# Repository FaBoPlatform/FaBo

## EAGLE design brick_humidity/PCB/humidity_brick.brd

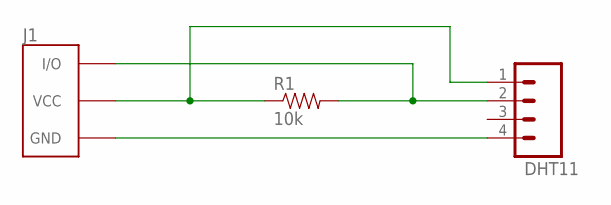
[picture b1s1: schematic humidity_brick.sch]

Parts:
J1: BRICK_3PIN
JP1: DHT11; 1X04_LONGPADS
R1: 10k; AXIAL-0.4

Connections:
GND: J1.GND, JP1.4
unnamed: J1.IN/OUT (I/O), JP1.2, R1.P$2 (2)
unnamed: J1.VCC, JP1.1, R1.P$1 (1)

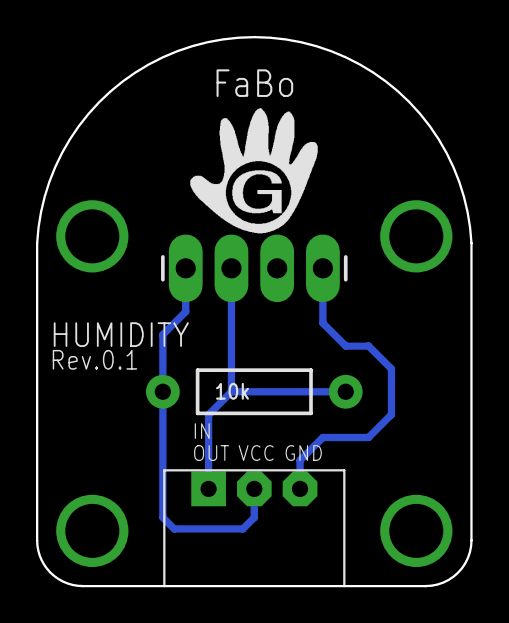
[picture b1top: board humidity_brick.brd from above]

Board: 2 copper layers, 24.1 x 30.5 mm, 3 parts (0 on the bottom side), 3 nets.

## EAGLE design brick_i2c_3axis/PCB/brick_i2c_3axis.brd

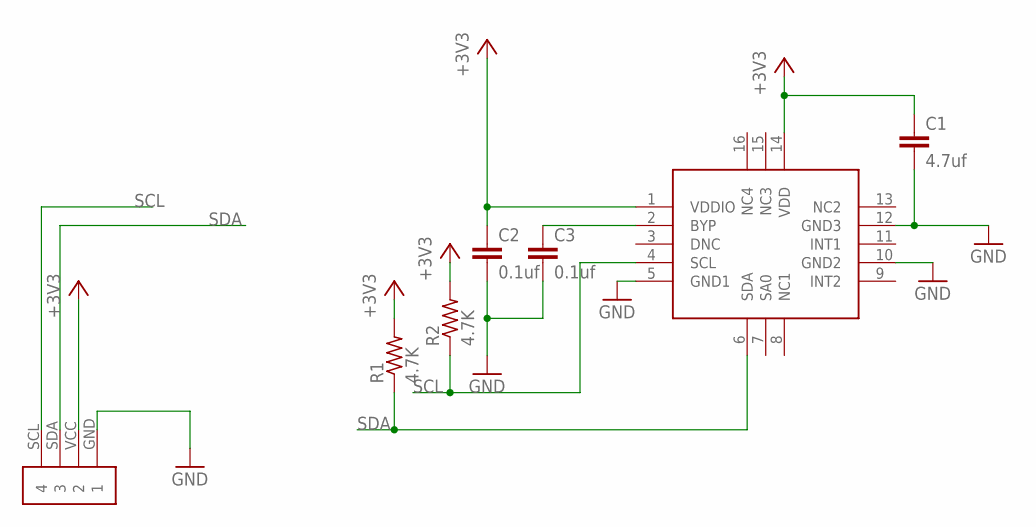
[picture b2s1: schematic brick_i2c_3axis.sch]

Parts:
C1: 4.7uf; C0603
C2, C3: 0.1uf; C0603
MMA1: FREESCALE-MMA8451Q
R1, R2: 4.7K; R0603
U$1: BRICK_I2C

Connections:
+3V3: C1.1, C2.1, MMA1.1 (VDDIO), MMA1.14 (VDD), R1.2, R2.2, U$1.VCC (2)
GND: C1.2, C2.2, C3.2, MMA1.5 (GND1), MMA1.10 (GND2), MMA1.12 (GND3), U$1.GND (1)
unnamed: C3.1, MMA1.2 (BYP)
SCL: MMA1.4 (SCL), R2.1, U$1.SCL (4)
SDA: MMA1.6 (SDA), R1.1, U$1.SDA (3)

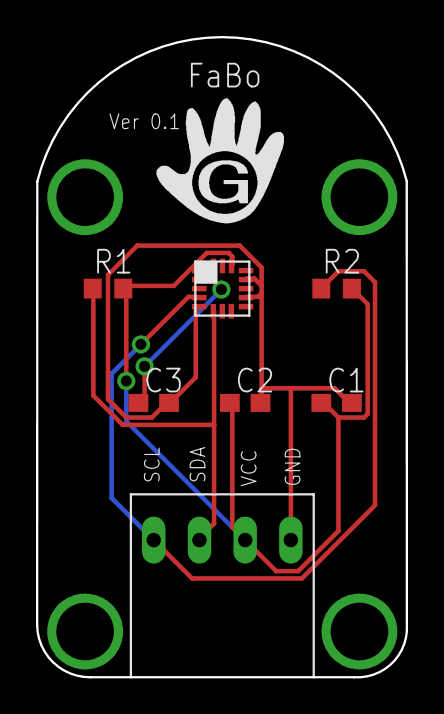
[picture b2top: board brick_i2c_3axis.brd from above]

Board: 2 copper layers, 20.5 x 35.6 mm, 7 parts (0 on the bottom side), 5 nets.

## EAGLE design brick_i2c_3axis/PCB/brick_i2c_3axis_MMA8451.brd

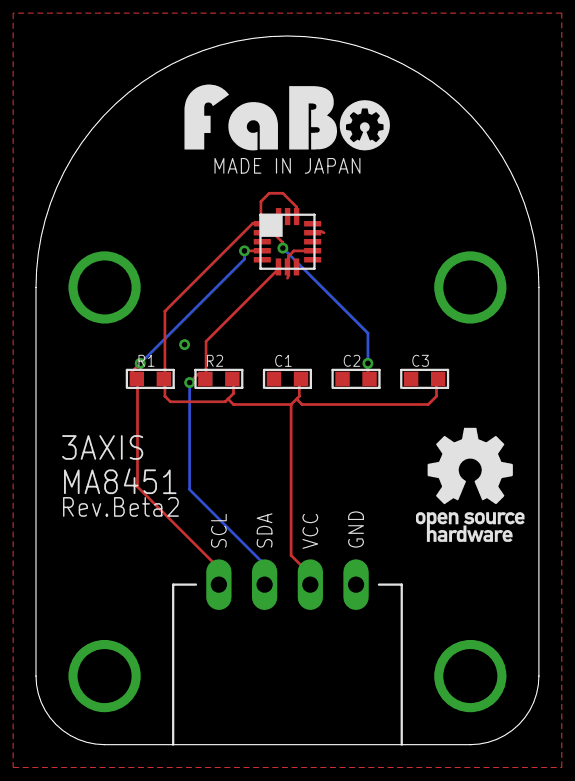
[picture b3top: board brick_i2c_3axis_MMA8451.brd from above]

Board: 2 copper layers, 27.9 x 39.4 mm, 9 parts (0 on the bottom side), 5 nets.

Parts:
C1, C2: 0.1uf; 0603
C3: 4.7uf; 0603
J1: BRICK_I2C
MMA1: FREESCALE-MMA8451Q
R1, R2: 4.7K; 0603
U$1: LOGO_OSHW_T_M
U$3: LOGO_FABO_M

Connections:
+3V3: C1.2, C3.2, J1.VCC, MMA1.1, MMA1.14, R1.2, R2.2
GND: C1.1, C2.1, C3.1, J1.GND, MMA1.5, MMA1.7, MMA1.10, MMA1.12
unnamed: C2.2, MMA1.2
SCL: J1.SCL, MMA1.4, R1.1
SDA: J1.SDA, MMA1.6, R2.1

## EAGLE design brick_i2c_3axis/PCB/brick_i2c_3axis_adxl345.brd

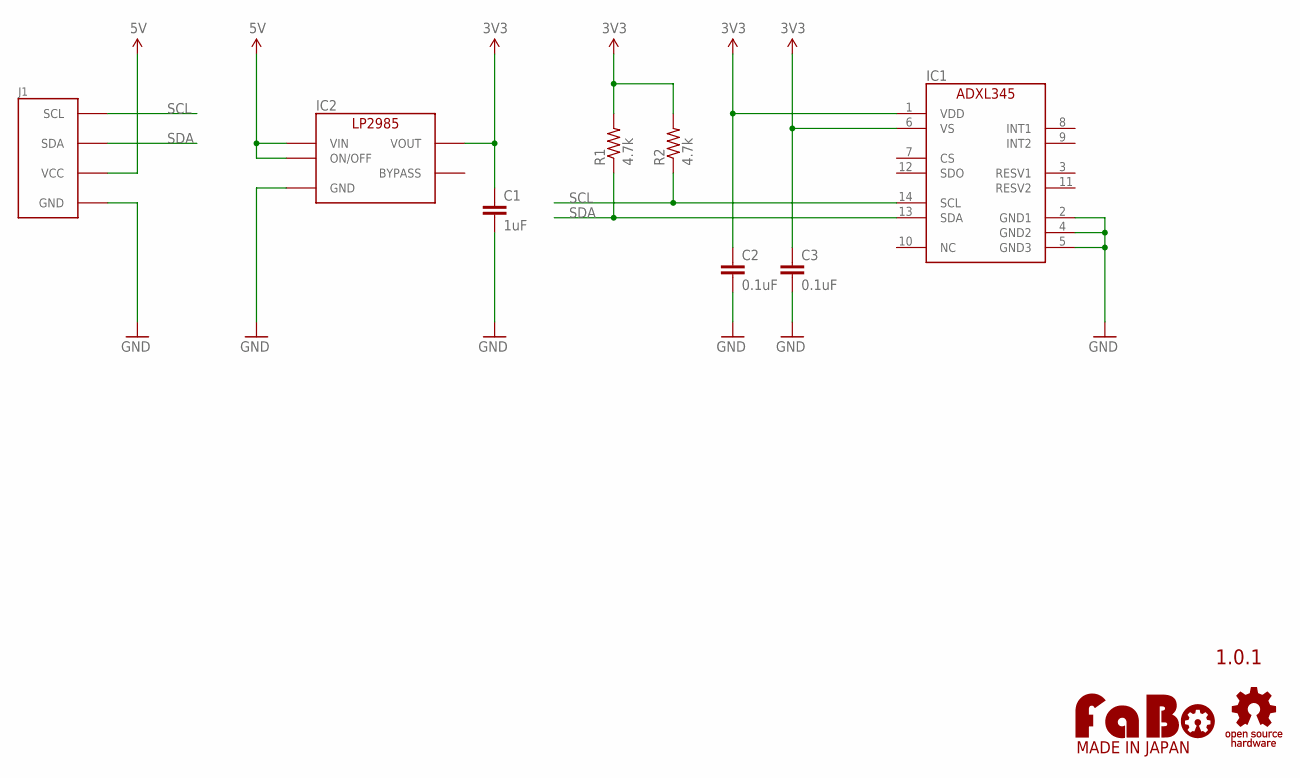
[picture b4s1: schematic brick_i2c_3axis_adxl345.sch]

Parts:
C1: 1uF; EIA0603
C2, C3: 0.1uF; EIA0603
IC1: AD-ADXL345; ANALOGDEVICES-ADXL345
IC2: TI-LP2985-33DBVR; TI-LP2985
J1: FABO_BRICK_I2C
R1, R2: 4.7k; EIA0603
U$2: LOGO_OSHW-T_M; LOGO_OSHW_T_M
U$3: LOGO_FABO-M; LOGO_FABO_M

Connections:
3V3: C1.1, C2.1, C3.1, IC1.1 (VDD), IC1.6 (VS), IC2.5 (VOUT), R1.2, R2.2
5V: IC2.1 (VIN), IC2.3 (ON/OFF), J1.VCC
GND: C1.2, C2.2, C3.2, IC1.2 (GND1), IC1.4 (GND2), IC1.5 (GND3), IC2.2 (GND), J1.GND
SCL: IC1.14 (SCL), J1.SCL, R2.1
SDA: IC1.13 (SDA), J1.SDA, R1.1

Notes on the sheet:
1.0.1

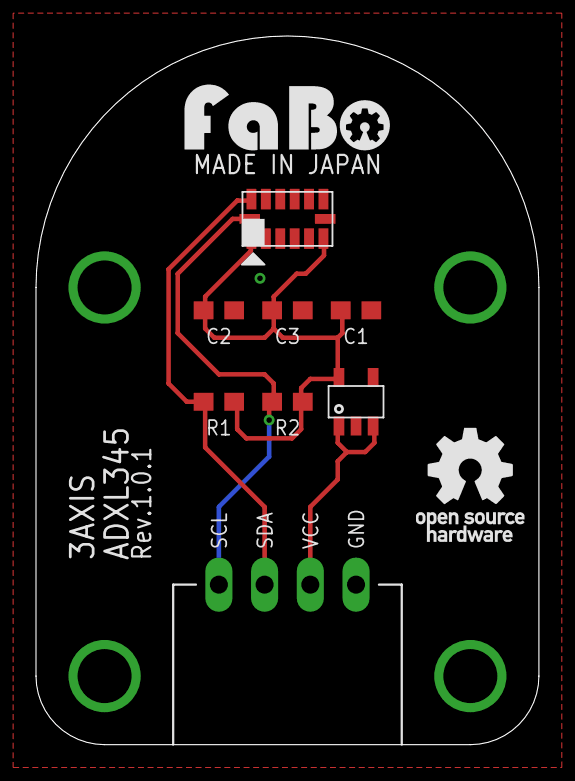
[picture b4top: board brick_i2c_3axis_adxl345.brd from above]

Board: 2 copper layers, 27.9 x 39.4 mm, 10 parts (0 on the bottom side), 5 nets.

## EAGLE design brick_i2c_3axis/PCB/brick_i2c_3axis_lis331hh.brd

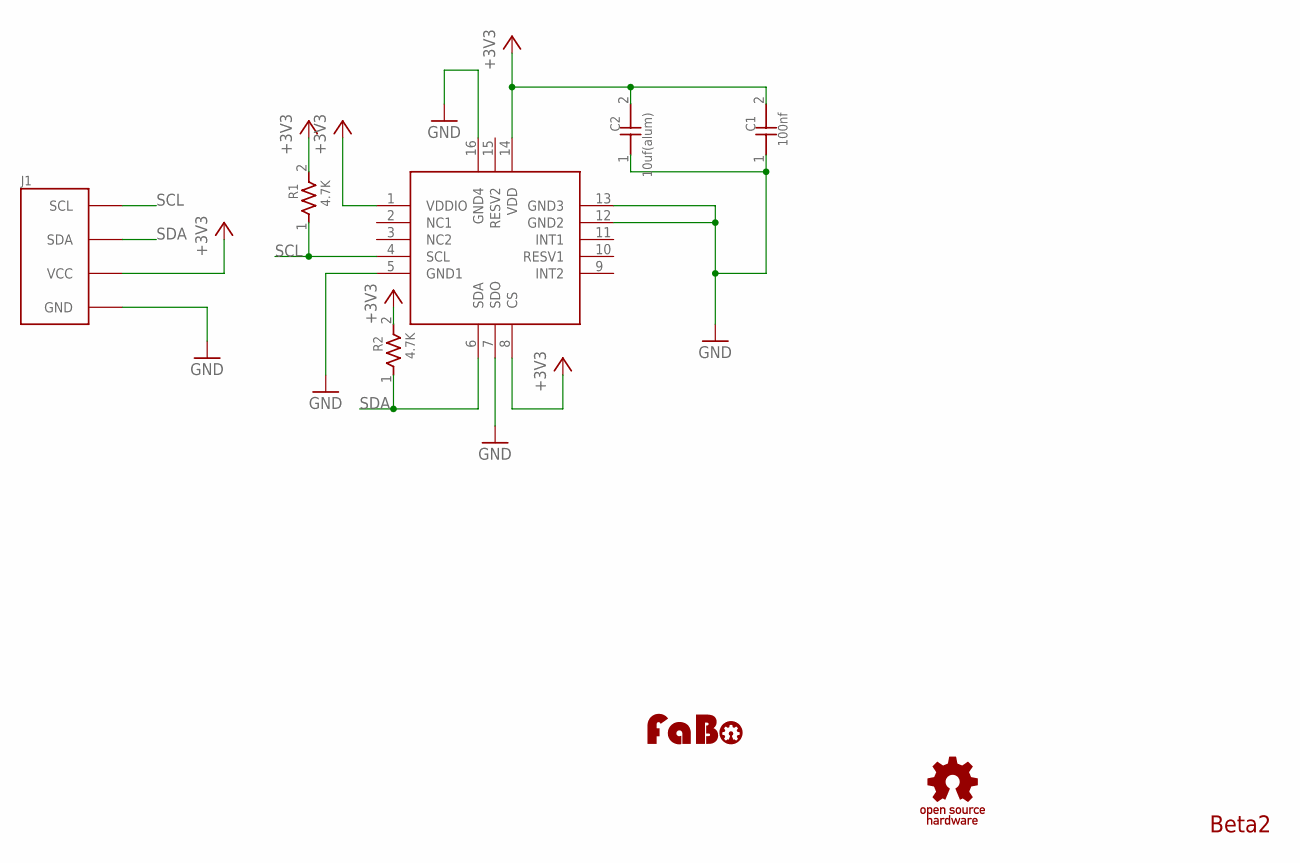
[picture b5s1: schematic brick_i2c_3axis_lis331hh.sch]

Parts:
C1: 100nf; 0603
C2: 10uf(alum); 0603
J1: BRICK_I2C
R1, R2: 4.7K; 0603
U$1: ST-LIS331HH
U$3: LOGO_OSHW_T-M; LOGO_OSHW_T_M
U$4: LOGO_FABO-M; LOGO_FABO_M

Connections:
+3V3: C1.2, C2.2, J1.VCC, R1.2, R2.2, U$1.1 (VDDIO), U$1.8 (CS), U$1.14 (VDD)
GND: C1.1, C2.1, J1.GND, U$1.5 (GND1), U$1.7 (SDO), U$1.12 (GND2), U$1.13 (GND3), U$1.16 (GND4)
SCL: J1.SCL, R1.1, U$1.4 (SCL)
SDA: J1.SDA, R2.1, U$1.6 (SDA)

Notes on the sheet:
Beta2

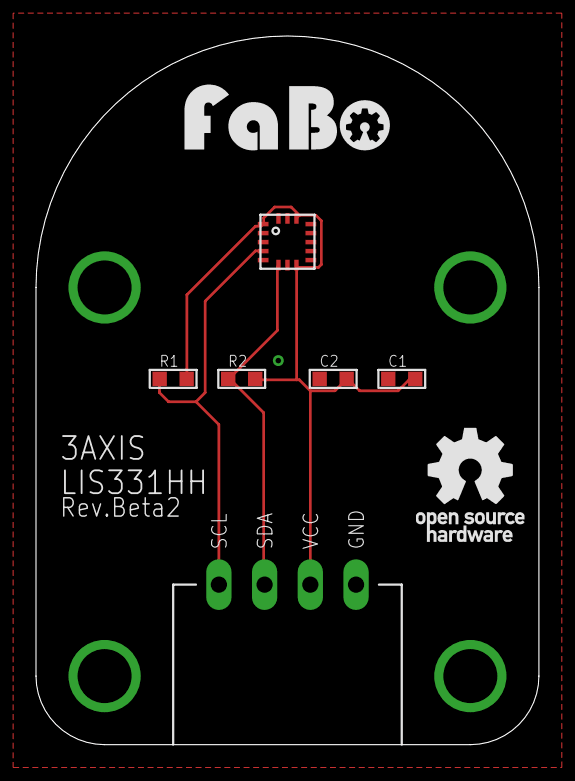
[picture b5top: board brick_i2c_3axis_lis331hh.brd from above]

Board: 2 copper layers, 27.9 x 39.4 mm, 8 parts (0 on the bottom side), 4 nets.

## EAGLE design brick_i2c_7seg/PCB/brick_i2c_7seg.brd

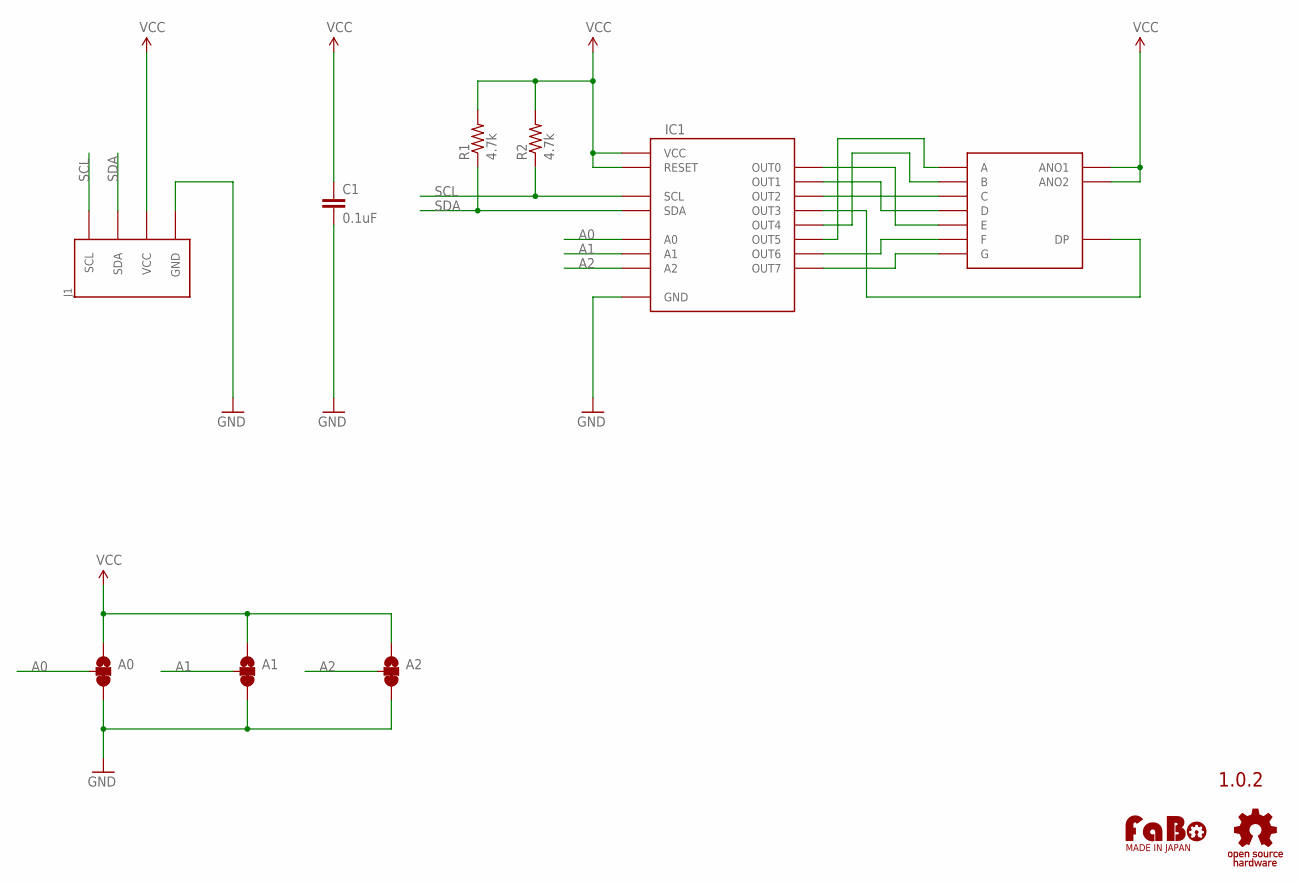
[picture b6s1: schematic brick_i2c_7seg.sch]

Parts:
A0, A1, A2: SMD-JUMPER-3-23SHORT; SMD-JUMPER-3
C1: 0.1uF; EIA0603
IC1: TLC59208F; TSSOP16
J1: BRICK_I2C
R1, R2: 4.7k; EIA0603
U$2: A-551SRD
U$3: LOGO_FABO-M; LOGO_FABO_M
U$4: LOGO_OSHW_T-BT; LOGO_OSHW_T_M_BOTTOM

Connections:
A0: A0.2, IC1.1 (A0)
A1: A1.2, IC1.2 (A1)
A2: A2.2, IC1.3 (A2)
GND: A0.3, A1.3, A2.3, C1.2, IC1.8 (GND), J1.GND
unnamed: IC1.4 (OUT0), U$2.E
unnamed: IC1.5 (OUT1), U$2.D
unnamed: IC1.6 (OUT2), U$2.C
unnamed: IC1.7 (OUT3), U$2.DP
unnamed: IC1.9 (OUT4), U$2.B
unnamed: IC1.10 (OUT5), U$2.A
unnamed: IC1.11 (OUT6), U$2.F
unnamed: IC1.12 (OUT7), U$2.G
SCL: IC1.14 (SCL), J1.SCL, R2.1
SDA: IC1.15 (SDA), J1.SDA, R1.1
VCC: A0.1, A1.1, A2.1, C1.1, IC1.13 (RESET), IC1.16 (VCC), J1.VCC, R1.2, R2.2, U$2.ANO1, U$2.ANO2

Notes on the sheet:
1.0.2

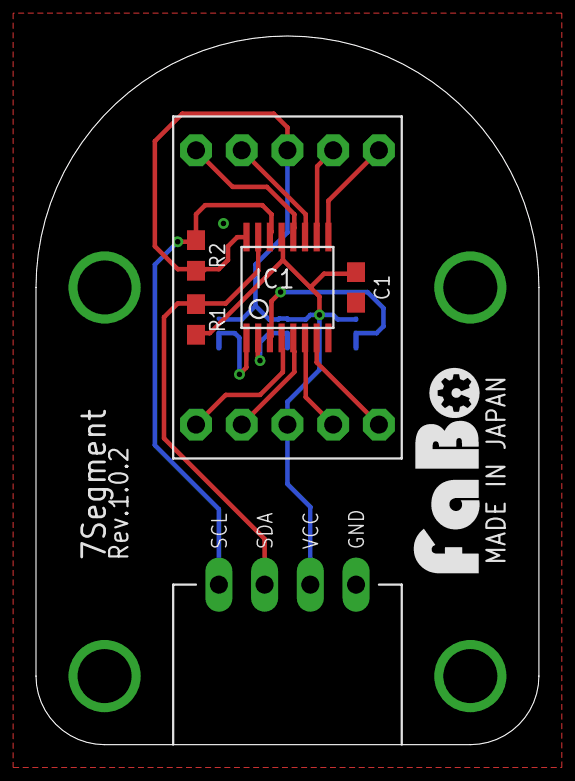
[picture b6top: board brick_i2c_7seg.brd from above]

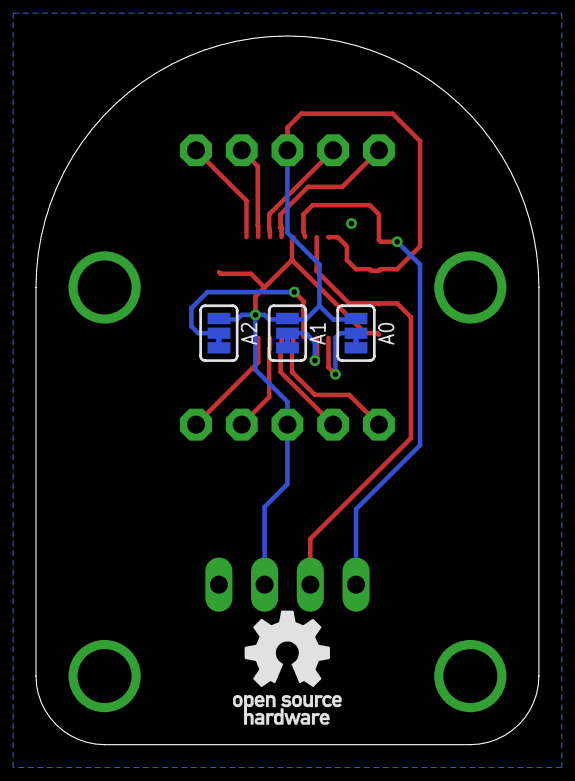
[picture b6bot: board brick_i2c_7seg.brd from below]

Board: 2 copper layers, 27.9 x 39.4 mm, 11 parts (3 on the bottom side), 15 nets.

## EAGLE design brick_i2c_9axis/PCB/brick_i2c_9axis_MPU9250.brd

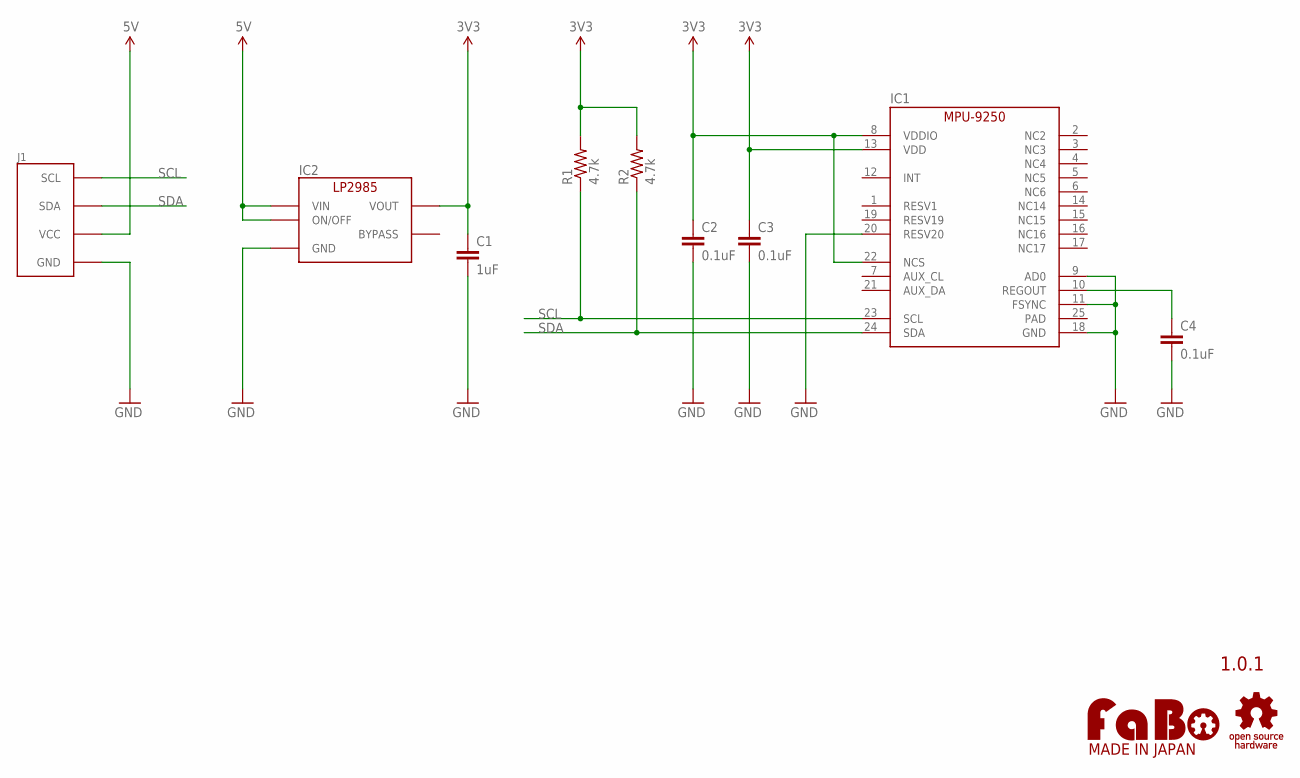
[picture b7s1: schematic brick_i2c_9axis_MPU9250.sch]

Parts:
C1: 1uF; EIA0603
C2, C3, C4: 0.1uF; EIA0603
IC1: IS-MPU9250; INVENSENSE-MPU9250
IC2: TI-LP2985-33DBVR; TI-LP2985
J1: FABO_BRICK_I2C
R1, R2: 4.7k; EIA0603
U$2: LOGO_OSHW-T_M; LOGO_OSHW_T_M
U$3: LOGO_FABO-M; LOGO_FABO_M

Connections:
3V3: C1.1, C2.1, C3.1, IC1.8 (VDDIO), IC1.13 (VDD), IC1.22 (NCS), IC2.5 (VOUT), R1.2, R2.2
5V: IC2.1 (VIN), IC2.3 (ON/OFF), J1.VCC
GND: C1.2, C2.2, C3.2, C4.2, IC1.9 (AD0), IC1.11 (FSYNC), IC1.18 (GND), IC1.20 (RESV20), IC2.2 (GND), J1.GND
unnamed: C4.1, IC1.10 (REGOUT)
SCL: IC1.23 (SCL), J1.SCL, R1.1
SDA: IC1.24 (SDA), J1.SDA, R2.1

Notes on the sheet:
1.0.1

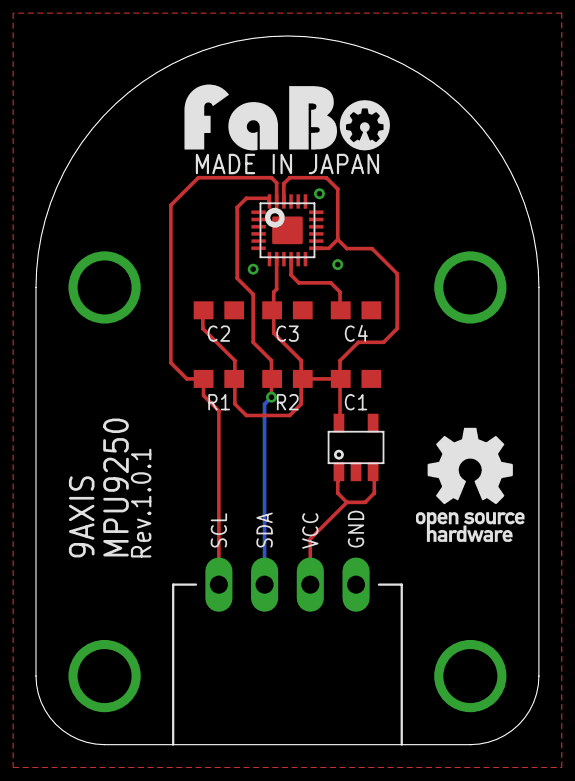
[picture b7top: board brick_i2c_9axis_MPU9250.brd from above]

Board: 2 copper layers, 27.9 x 39.4 mm, 11 parts (0 on the bottom side), 6 nets.

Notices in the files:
parts and their libraries:
SparkFun-Connectors: Licensing: Creative Commons ShareAlike 4.0 International - https://creativecommons.org/licenses/by-sa/4.0
FaBo-etc: Released under the Creative Commons Attribution-ShareAlike 4.0 License
https://creativecommons.org/licenses/by-sa/4.0
GClue: Released under the Creative Commons
